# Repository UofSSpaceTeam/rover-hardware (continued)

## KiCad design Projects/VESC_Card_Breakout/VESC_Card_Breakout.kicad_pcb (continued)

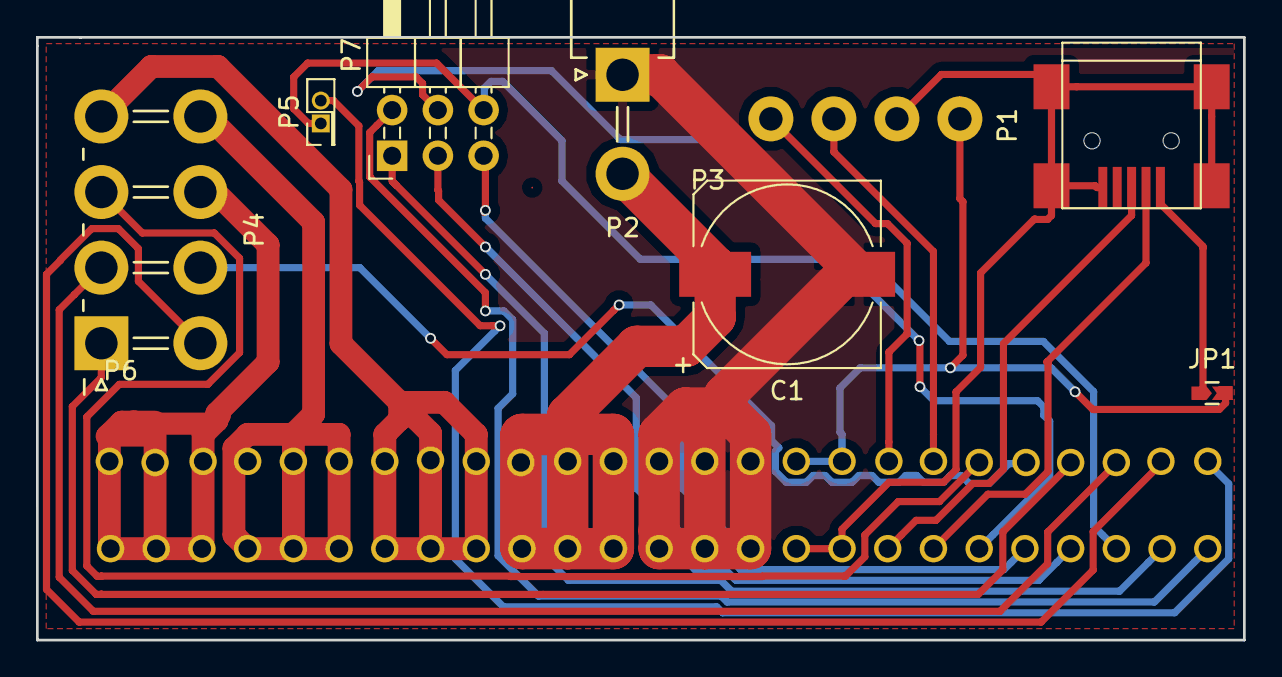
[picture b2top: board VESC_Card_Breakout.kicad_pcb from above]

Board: 2 copper layers, 67.1 x 33.5 mm, 9 parts (0 on the bottom side), 24 nets.

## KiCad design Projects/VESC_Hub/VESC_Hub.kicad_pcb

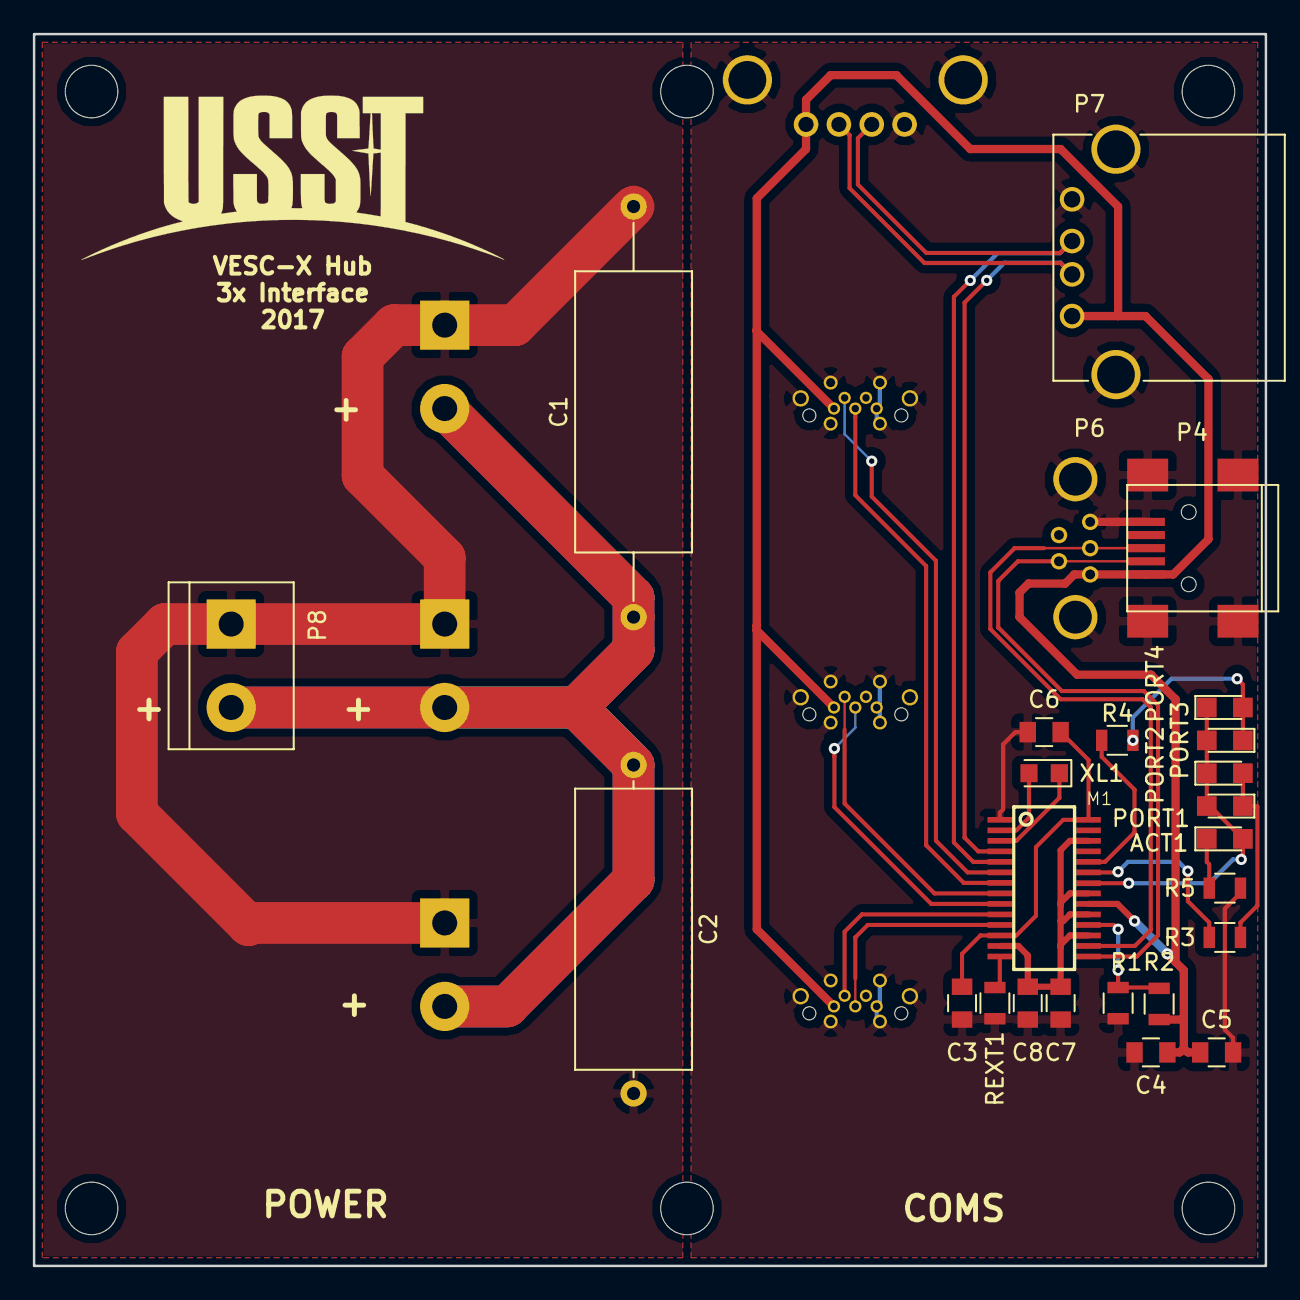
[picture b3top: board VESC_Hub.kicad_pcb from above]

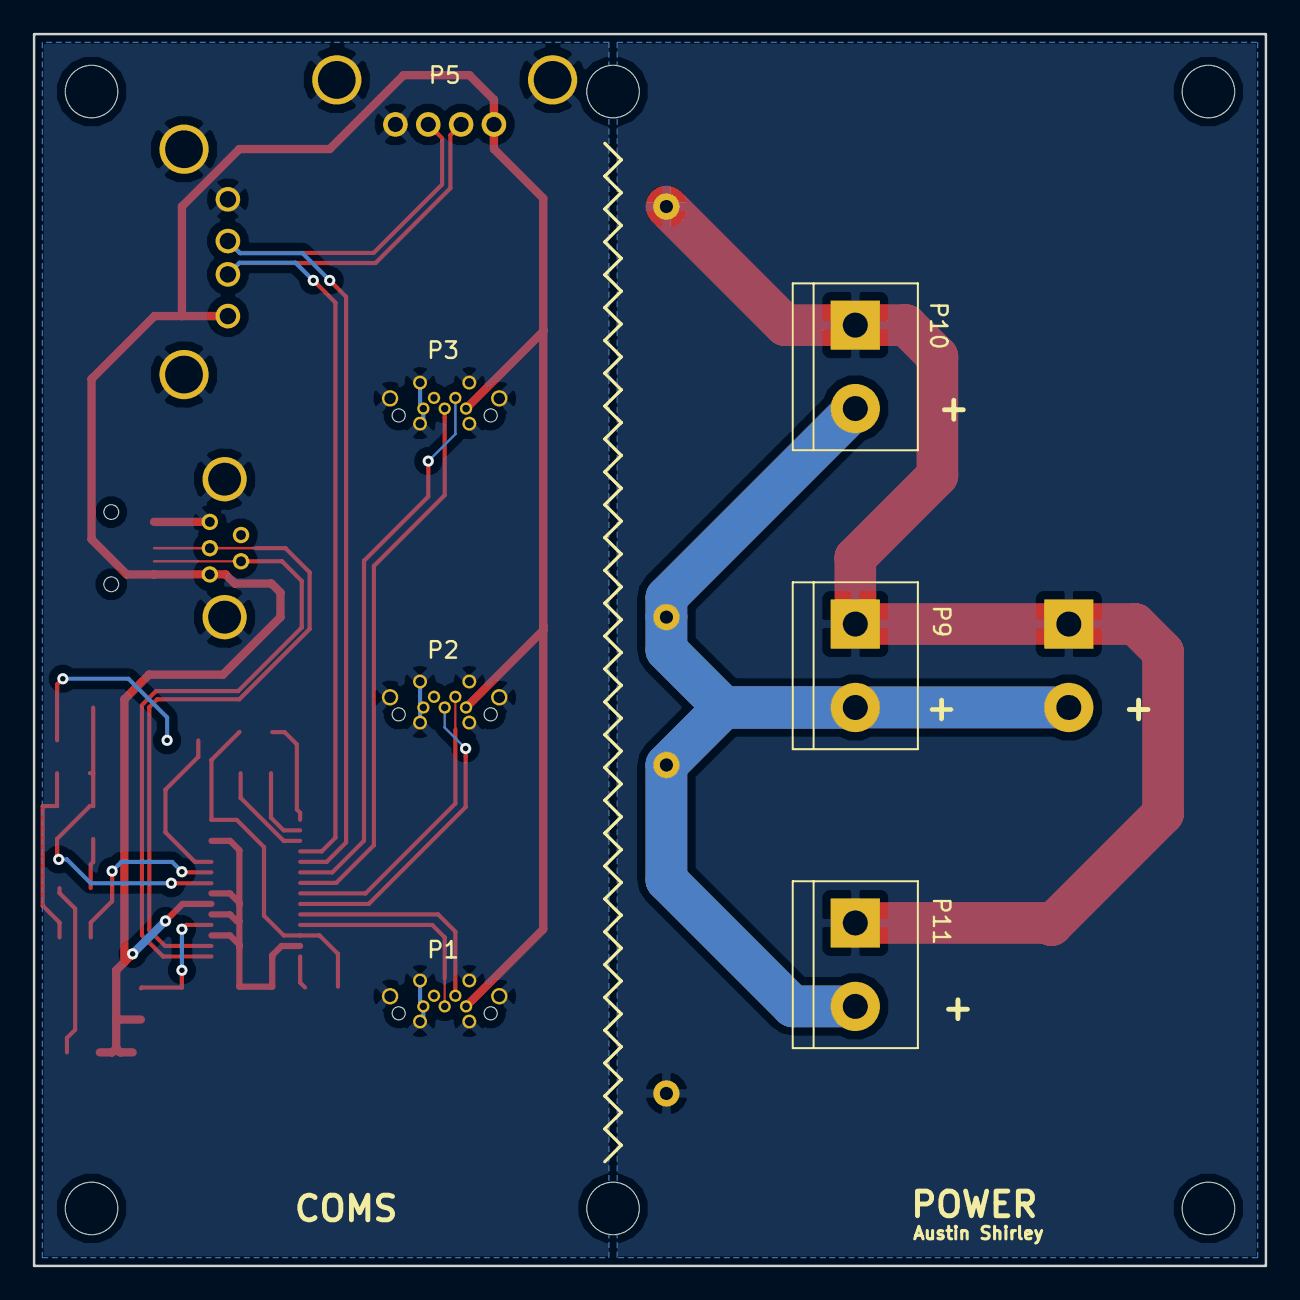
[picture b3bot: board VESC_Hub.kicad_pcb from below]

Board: 2 copper layers, 75.0 x 75.0 mm, 32 parts (7 on the bottom side), 26 nets.

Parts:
ACT1: LED_0805
C1: 2000u; C_Axial_L17.0mm_D7.0mm_P25.00mm_Horizontal
C2: 2000u; C_Axial_L17.0mm_D7.0mm_P20.00mm_Horizontal
C3, C4, C7: 10uF; C_0805
C5, C6, C8: 0.1uF; C_0805
M1: FE1.1S; FE1.1S_SSOP-28
P1: USB_OTG_M1; USB3150_Micro_Vertical
P2: USB_OTG_M2; USB3150_Micro_Vertical
P3: USB_OTG_M3; USB3150_Micro_Vertical
P4: USB_OTG_UP; USB_Mini-B
P5: USB_DS; WRCOM_USB_A_VERT
P6: USB_OTG_UP; WRCOM_MINI_USB_VERT
P7: USB_DS; USB_A
P8: POWER_IN; bornier2
P9: M1; bornier2
P10: M2; bornier2
P11: M3; bornier2
PORT1, PORT2, PORT3, PORT4: LED_0805
R1: 100K; R_0805
R2: 47K; R_0805
R3, R4, R5: 330; R_0805
REXT1: 2.7K; R_0805
XL1: 12MHz; Crystal_SMD_2012-2pin_2.0x1.2mm_HandSoldering

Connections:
+5V: C4.1, C5.1, M1.20, P1.1, P2.1, P3.1, P4.1, P5.1, P6.1, P7.1, R2.1
+24V: C1.1, C2.1, P8.2, P9.2, P10.2, P11.2
/USB1_N: M1.4, P5.2, P7.2
/USB1_P: M1.5, P5.3, P7.3
/USB2_N: M1.6, P3.2
/USB2_P: M1.7, P3.3
/USB3_N: M1.8, P2.2
/USB3_P: M1.9, P2.3
/USB4_N: M1.10, P1.2
/USB4_P: M1.11, P1.3
/USBUP_N: M1.15, P4.2, P6.2
/USBUP_P: M1.16, P4.3, P6.3
GND: C1.2, C2.2, P8.1, P9.1, P10.1, P11.1
GNDD: C3.2, C4.2, C5.2, C6.2, C7.2, C8.2, M1.1, P1.5, P1.6, P2.5, P2.6, P3.5, P3.6, P4.5, P4.6, P5.4, P5.5, P6.5, P6.6, P7.4, P7.5, R1.2, R5.2, REXT1.1
unnamed: ACT1.1, R5.1
unnamed: ACT1.2, M1.22, PORT1.2, PORT2.1, PORT3.2, PORT4.1
unnamed: C3.1, C6.1, M1.12, M1.28
unnamed: M1.2, XL1.2
unnamed: M1.3, XL1.1
unnamed: M1.14, REXT1.2
unnamed: M1.18, R1.1, R2.2
unnamed: M1.23, R3.1
unnamed: M1.24, R4.1
unnamed: PORT1.1, PORT2.2, R3.2
unnamed: PORT3.1, PORT4.2, R4.2
VDD: C7.1, C8.1, M1.13, M1.17, M1.19, M1.21, M1.26

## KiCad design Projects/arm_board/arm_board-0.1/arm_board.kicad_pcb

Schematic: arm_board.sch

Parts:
DEMUX1: 74HC138; SO-16-N
MUX1, MUX2, MUX3: 74HC4051; SO-16-N
P3, P4: CONN_2; MiniFitJr_2-pin_0039310028
U1: TLV150X; SO-16-N
U2: 7805; MC7805CDTRKG
U56: 2534-6002UB_34-pin_header; 34-pin_2534-6002UB

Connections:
12V: P3.1, U2.1; also elsewhere on the board
/EOC_MCU: U1.4 (EOC), U56.26
/MCU_FS: U1.13 (FS), U56.14
/MCU_SCLK: U1.3 (SCLK), U56.8
/MCU_SDI: U1.1 (SDO), U56.12
/MCU_SDO: U1.2 (SDI), U56.10
/OIL_ss/CLR: U56.6; also elsewhere on the board
/OIL_ss/D: U56.4; also elsewhere on the board
/OIL_ss/EN: U56.2; also elsewhere on the board
/OIL_ss/MCU_PWM0: U56.9; also elsewhere on the board
/OIL_ss/MCU_PWM1: U56.11; also elsewhere on the board
/OIL_ss/MCU_PWM2: U56.13; also elsewhere on the board
/OIL_ss/MCU_PWM3: U56.15; also elsewhere on the board
/OIL_ss/MCU_PWM4: U56.17; also elsewhere on the board
/OIL_ss/MCU_PWM5: U56.19; also elsewhere on the board
/OIL_ss/MCU_PWM6: U56.21; also elsewhere on the board
/OIL_ss/MCU_PWM7: U56.23; also elsewhere on the board
/OIL_ss/S0: DEMUX1.1 (A0), MUX1.11 (S0), MUX2.11 (S0), MUX3.11 (S0), U56.16; also elsewhere on the board
/OIL_ss/S1: DEMUX1.2 (A1), MUX1.10 (S1), MUX2.10 (S1), MUX3.10 (S1), U56.18; also elsewhere on the board
/OIL_ss/S2: DEMUX1.3 (A2), MUX1.9 (S2), MUX2.9 (S2), MUX3.9 (S2), U56.20; also elsewhere on the board
/OVRFLW: MUX2.3 (Z), U56.27
/Q_CNT: MUX1.3 (Z), U56.25
/RST: DEMUX1.6 (E3), U56.31
/UDRFLW: MUX3.3 (Z), U56.29
/VNH3SP30 Motor SS 1/CNT_OVRFLW: MUX2.14 (Y1); also elsewhere on the board
/VNH3SP30 Motor SS 1/CNT_S0: U56.1; also elsewhere on the board
/VNH3SP30 Motor SS 1/CNT_S1: U56.3; also elsewhere on the board
/VNH3SP30 Motor SS 1/CNT_S2: U56.5; also elsewhere on the board
/VNH3SP30 Motor SS 1/CNT_S3: U56.7; also elsewhere on the board
/VNH3SP30 Motor SS 1/CNT_UDRFLW: MUX3.14 (Y1); also elsewhere on the board
/VNH3SP30 Motor SS 1/Q_CNT: MUX1.14 (Y1); also elsewhere on the board
/VNH3SP30 Motor SS 1/n_CNT_RESET: DEMUX1.14 (n_Y1); also elsewhere on the board
/VNH3SP30 Motor SS 2/CNT_OVRFLW: MUX2.15 (Y2); also elsewhere on the board
/VNH3SP30 Motor SS 2/CNT_UDRFLW: MUX3.15 (Y2); also elsewhere on the board
/VNH3SP30 Motor SS 2/Q_CNT: MUX1.15 (Y2); also elsewhere on the board
/VNH3SP30 Motor SS 2/n_CNT_RESET: DEMUX1.13 (n_Y2); also elsewhere on the board
/VNH3SP30 Motor SS 3/CNT_OVRFLW: MUX2.12 (Y3); also elsewhere on the board
/VNH3SP30 Motor SS 3/CNT_UDRFLW: MUX3.12 (Y3); also elsewhere on the board
/VNH3SP30 Motor SS 3/Q_CNT: MUX1.12 (Y3); also elsewhere on the board
/VNH3SP30 Motor SS 3/n_CNT_RESET: DEMUX1.12 (n_Y3); also elsewhere on the board
/VNH3SP30 Motor SS 4/CNT_OVRFLW: MUX2.1 (Y4); also elsewhere on the board
/VNH3SP30 Motor SS 4/CNT_UDRFLW: MUX3.1 (Y4); also elsewhere on the board
/VNH3SP30 Motor SS 4/Q_CNT: MUX1.1 (Y4); also elsewhere on the board
/VNH3SP30 Motor SS 4/n_CNT_RESET: DEMUX1.11 (n_Y4); also elsewhere on the board
/VNH3SP30 Motor SS 5/CNT_OVRFLW: MUX2.5 (Y5); also elsewhere on the board
/VNH3SP30 Motor SS 5/CNT_UDRFLW: MUX3.5 (Y5); also elsewhere on the board
/VNH3SP30 Motor SS 5/Q_CNT: MUX1.5 (Y5); also elsewhere on the board
/VNH3SP30 Motor SS 5/n_CNT_RESET: DEMUX1.10 (n_Y5); also elsewhere on the board
/VNH3SP30 SS 1/WPR: U1.6 (A0), U56.33; also elsewhere on the board
/VNH3SP30 SS 2/WPR: U1.7 (A1), U56.32; also elsewhere on the board
/n_ADC_CS: U1.16 (n_CS), U56.24
/n_ADC_CSTART: U1.10 (n_CSTART), U56.22
/vnh3sp30_motorLinac_ss/CNT_OVRFLW: MUX2.13 (Y0); also elsewhere on the board
/vnh3sp30_motorLinac_ss/CNT_UDRFLW: MUX3.13 (Y0); also elsewhere on the board
/vnh3sp30_motorLinac_ss/Q_CNT: MUX1.13 (Y0); also elsewhere on the board
/vnh3sp30_motorLinac_ss/WPR: U1.8 (A2), U56.34; also elsewhere on the board
/vnh3sp30_motorLinac_ss/n_CNT_RESET: DEMUX1.15 (n_Y0); also elsewhere on the board
GND_12V: P3.2 (PM), U2.2; also elsewhere on the board
NOISE_5V: U2.3; also elsewhere on the board
unnamed 225: DEMUX1.7 (n_Y7); also elsewhere on the board
unnamed 226: DEMUX1.9 (n_Y6); also elsewhere on the board
Whiper_GND: U1.14 (REFM), U56.28; also elsewhere on the board
Whiper_V++: U1.15 (REFP), U56.30; also elsewhere on the board

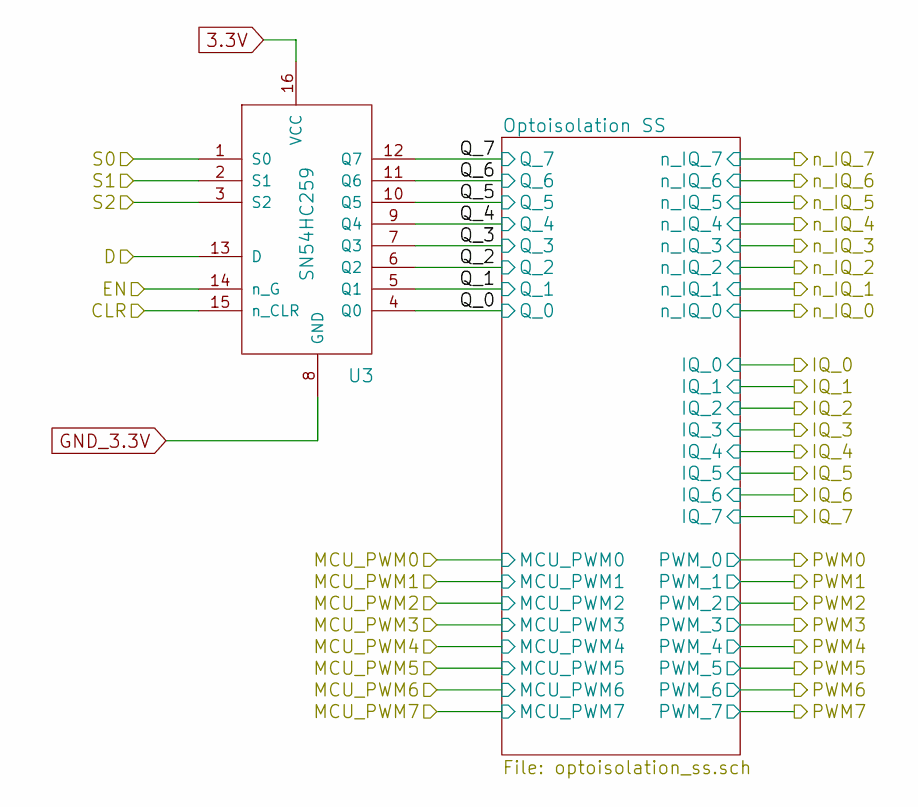
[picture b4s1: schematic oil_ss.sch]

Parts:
U3: SN54HC259; SO-16-N

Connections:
/OIL_ss/CLR: U3.15 (n_CLR); also elsewhere on the board
/OIL_ss/D: U3.13 (D); also elsewhere on the board
/OIL_ss/EN: U3.14 (n_G); also elsewhere on the board
/OIL_ss/Optoisolation SS/Q_0: U3.4 (Q0); also elsewhere on the board
/OIL_ss/Optoisolation SS/Q_1: U3.5 (Q1); also elsewhere on the board
/OIL_ss/Optoisolation SS/Q_2: U3.6 (Q2); also elsewhere on the board
/OIL_ss/Optoisolation SS/Q_3: U3.7 (Q3); also elsewhere on the board
/OIL_ss/Optoisolation SS/Q_4: U3.9 (Q4); also elsewhere on the board
/OIL_ss/Optoisolation SS/Q_5: U3.10 (Q5); also elsewhere on the board
/OIL_ss/Optoisolation SS/Q_6: U3.11 (Q6); also elsewhere on the board
/OIL_ss/Optoisolation SS/Q_7: U3.12 (Q7); also elsewhere on the board
/OIL_ss/S0: U3.1 (S0); also elsewhere on the board
/OIL_ss/S1: U3.2 (S1); also elsewhere on the board
/OIL_ss/S2: U3.3 (S2); also elsewhere on the board

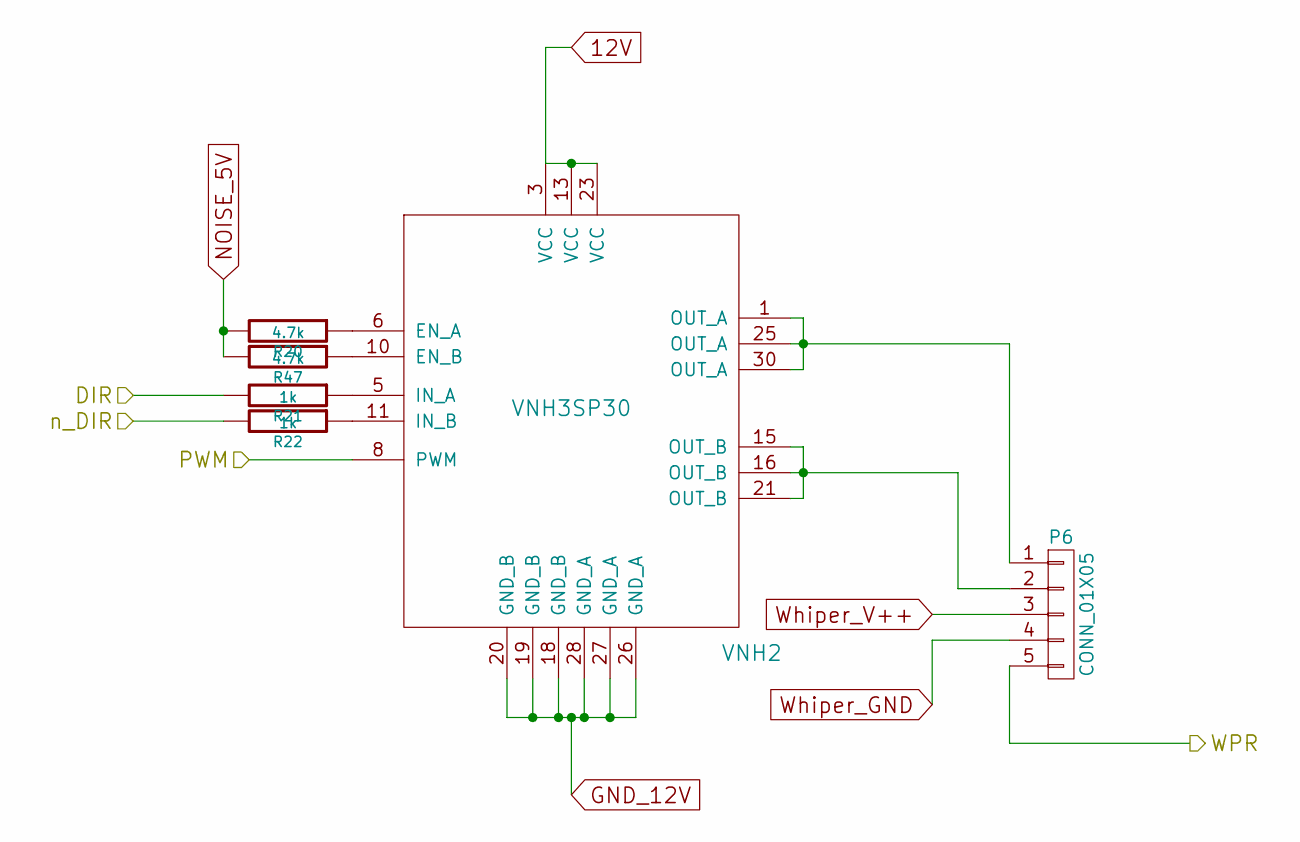
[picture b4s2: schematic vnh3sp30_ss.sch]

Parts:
P5: CONN_01X05; 5-pin_640467-1
R17, R46: 4.7k; R_0805
R18, R22: 1k; R_0805
VNH1: VNH3SP30; VNH3SP30TR-E

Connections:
12V: VNH1.3 (VCC), VNH1.13 (VCC), VNH1.23 (VCC); also elsewhere on the board
/VNH3SP30 SS 1/DIR: R18.2; also elsewhere on the board
/VNH3SP30 SS 1/PWM: VNH1.8 (PWM); also elsewhere on the board
/VNH3SP30 SS 1/WPR: P5.5; also elsewhere on the board
/VNH3SP30 SS 2/n_DIR: R22.2; also elsewhere on the board
GND_12V: VNH1.18 (GND_B), VNH1.19 (GND_B), VNH1.20 (GND_B), VNH1.26 (GND_A), VNH1.27 (GND_A), VNH1.28 (GND_A); also elsewhere on the board
NOISE_5V: R17.2, R46.2; also elsewhere on the board
unnamed: P5.1, VNH1.1 (OUT_A), VNH1.25 (OUT_A), VNH1.30 (OUT_A)
unnamed: P5.2, VNH1.15 (OUT_B), VNH1.16 (OUT_B), VNH1.21 (OUT_B)
unnamed: R17.1, VNH1.6 (EN_A)
unnamed: R18.1, VNH1.5 (IN_A)
unnamed: R46.1, VNH1.10 (EN_B)
Whiper_GND: P5.4; also elsewhere on the board
Whiper_V++: P5.3; also elsewhere on the board

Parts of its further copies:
P6: CONN_01X05; 5-pin_640467-1
R19, R21: 1k; R_0805
R20, R47: 4.7k; R_0805
VNH2: VNH3SP30; VNH3SP30TR-E

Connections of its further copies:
12V: VNH2.3 (VCC), VNH2.13 (VCC), VNH2.23 (VCC); also elsewhere on the board
/VNH3SP30 SS 1/n_DIR: R19.2; also elsewhere on the board
/VNH3SP30 SS 2/DIR: R21.2; also elsewhere on the board
/VNH3SP30 SS 2/PWM: VNH2.8 (PWM); also elsewhere on the board
/VNH3SP30 SS 2/WPR: P6.5; also elsewhere on the board
GND_12V: VNH2.18 (GND_B), VNH2.19 (GND_B), VNH2.20 (GND_B), VNH2.26 (GND_A), VNH2.27 (GND_A), VNH2.28 (GND_A); also elsewhere on the board
NOISE_5V: R20.2, R47.2; also elsewhere on the board
unnamed: P6.1, VNH2.1 (OUT_A), VNH2.25 (OUT_A), VNH2.30 (OUT_A)
unnamed: P6.2, VNH2.15 (OUT_B), VNH2.16 (OUT_B), VNH2.21 (OUT_B)
unnamed: R20.1, VNH2.6 (EN_A)
unnamed: R21.1, VNH2.5 (IN_A)
unnamed: R47.1, VNH2.10 (EN_B)
Whiper_GND: P6.4; also elsewhere on the board
Whiper_V++: P6.3; also elsewhere on the board

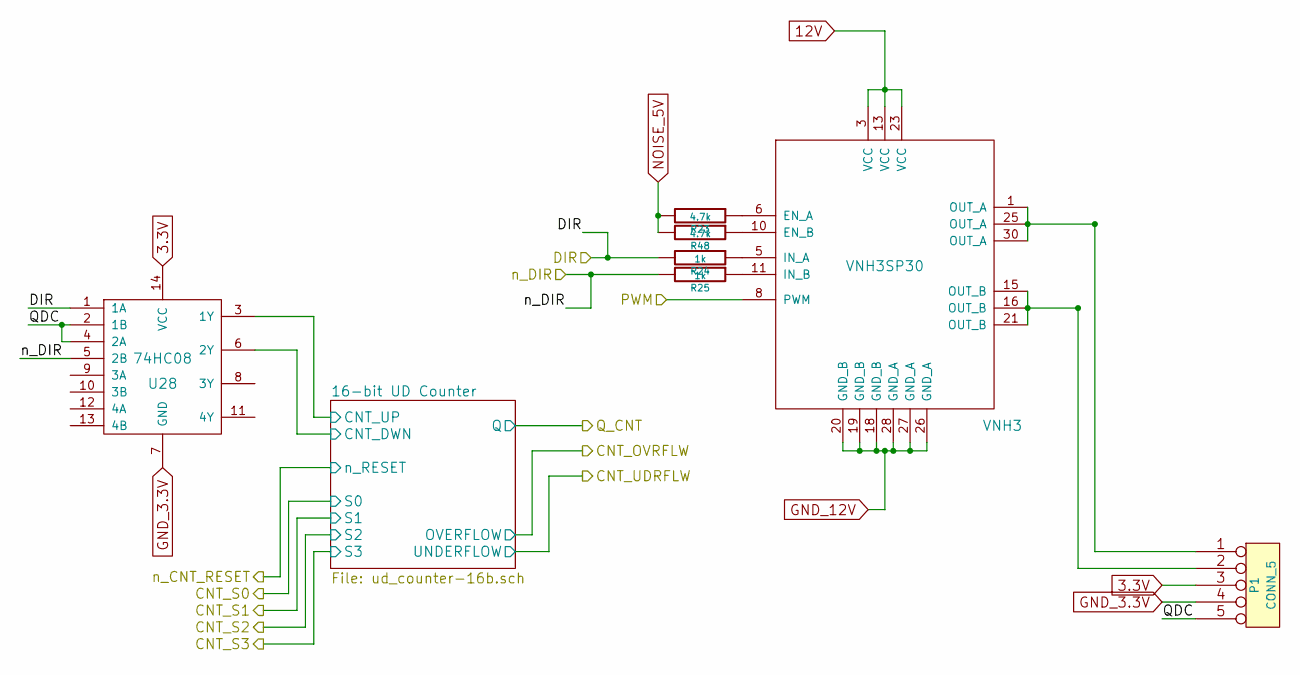
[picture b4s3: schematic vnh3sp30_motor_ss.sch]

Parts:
P1: CONN_5; 5-pin_640467-1
R23, R53: 4.7k; R_0805
R39, R40: 1k; R_0805
U28: 74HC08; SOIC-14
VNH3: VNH3SP30; VNH3SP30TR-E

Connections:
12V: VNH3.3 (VCC), VNH3.13 (VCC), VNH3.23 (VCC); also elsewhere on the board
/VNH3SP30 Motor SS 1/16-bit UD Counter/CNT_DWN: U28.6 (2Y); also elsewhere on the board
/VNH3SP30 Motor SS 1/16-bit UD Counter/CNT_UP: U28.3 (1Y); also elsewhere on the board
/VNH3SP30 Motor SS 1/PWM: VNH3.8 (PWM); also elsewhere on the board
/VNH3SP30 Motor SS 1/QDC: P1.5, U28.2 (1B), U28.4 (2A)
GND_12V: VNH3.18 (GND_B), VNH3.19 (GND_B), VNH3.20 (GND_B), VNH3.26 (GND_A), VNH3.27 (GND_A), VNH3.28 (GND_A); also elsewhere on the board
NOISE_5V: R23.2, R53.2; also elsewhere on the board
unnamed: P1.1, VNH3.1 (OUT_A), VNH3.25 (OUT_A), VNH3.30 (OUT_A)
unnamed: P1.2, VNH3.15 (OUT_B), VNH3.16 (OUT_B), VNH3.21 (OUT_B)
unnamed: R23.1, VNH3.6 (EN_A)

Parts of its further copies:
P2, P7, P8, P10: CONN_5; 5-pin_640467-1
R24, R25, R27, R28, R30, R31, R33, R34: 1k; R_0805
R26, R29, R32, R38, R48, R49, R50, R51: 4.7k; R_0805
U35, U42, U44, U58: 74HC08; SOIC-14
VNH4, VNH5, VNH6, VNH7: VNH3SP30; VNH3SP30TR-E

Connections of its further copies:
12V: VNH4.3 (VCC), VNH4.13 (VCC), VNH4.23 (VCC), VNH5.3 (VCC), VNH5.13 (VCC), VNH5.23 (VCC), VNH6.3 (VCC), VNH6.13 (VCC), VNH6.23 (VCC), VNH7.3 (VCC), VNH7.13 (VCC), VNH7.23 (VCC); also elsewhere on the board
/VNH3SP30 Motor SS 2/16-bit UD Counter/CNT_DWN: U58.6 (2Y); also elsewhere on the board
/VNH3SP30 Motor SS 2/16-bit UD Counter/CNT_UP: U58.3 (1Y); also elsewhere on the board
/VNH3SP30 Motor SS 2/PWM: VNH4.8 (PWM); also elsewhere on the board
/VNH3SP30 Motor SS 2/QDC: P10.5, U58.2 (1B), U58.4 (2A)
/VNH3SP30 Motor SS 3/16-bit UD Counter/CNT_DWN: U35.6 (2Y); also elsewhere on the board
/VNH3SP30 Motor SS 3/16-bit UD Counter/CNT_UP: U35.3 (1Y); also elsewhere on the board
/VNH3SP30 Motor SS 3/DIR: R27.2, U35.1 (1A); also elsewhere on the board
/VNH3SP30 Motor SS 3/PWM: VNH5.8 (PWM); also elsewhere on the board
/VNH3SP30 Motor SS 3/QDC: P2.5, U35.2 (1B), U35.4 (2A)
/VNH3SP30 Motor SS 3/n_DIR: R28.2, U35.5 (2B); also elsewhere on the board
/VNH3SP30 Motor SS 4/16-bit UD Counter/CNT_DWN: U44.6 (2Y); also elsewhere on the board
/VNH3SP30 Motor SS 4/16-bit UD Counter/CNT_UP: U44.3 (1Y); also elsewhere on the board
/VNH3SP30 Motor SS 4/DIR: R33.2, U44.1 (1A); also elsewhere on the board
/VNH3SP30 Motor SS 4/PWM: VNH7.8 (PWM); also elsewhere on the board
/VNH3SP30 Motor SS 4/QDC: P8.5, U44.2 (1B), U44.4 (2A)
/VNH3SP30 Motor SS 4/n_DIR: R34.2, U44.5 (2B); also elsewhere on the board
/VNH3SP30 Motor SS 5/16-bit UD Counter/CNT_DWN: U42.6 (2Y); also elsewhere on the board
/VNH3SP30 Motor SS 5/16-bit UD Counter/CNT_UP: U42.3 (1Y); also elsewhere on the board
/VNH3SP30 Motor SS 5/DIR: R30.2, U42.1 (1A); also elsewhere on the board
/VNH3SP30 Motor SS 5/PWM: VNH6.8 (PWM); also elsewhere on the board
/VNH3SP30 Motor SS 5/QDC: P7.5, U42.2 (1B), U42.4 (2A)
/VNH3SP30 Motor SS 5/n_DIR: R31.2, U42.5 (2B); also elsewhere on the board
GND_12V: VNH4.18 (GND_B), VNH4.19 (GND_B), VNH4.20 (GND_B), VNH4.26 (GND_A), VNH4.27 (GND_A), VNH4.28 (GND_A), VNH5.18 (GND_B), VNH5.19 (GND_B), VNH5.20 (GND_B), VNH5.26 (GND_A), VNH5.27 (GND_A), VNH5.28 (GND_A), VNH6.18 (GND_B), VNH6.19 (GND_B), VNH6.20 (GND_B), VNH6.26 (GND_A), VNH6.27 (GND_A), VNH6.28 (GND_A), VNH7.18 (GND_B), VNH7.19 (GND_B), VNH7.20 (GND_B), VNH7.26 (GND_A), VNH7.27 (GND_A), VNH7.28 (GND_A); also elsewhere on the board
NOISE_5V: R26.2, R29.2, R32.2, R38.2, R48.2, R49.2, R50.2, R51.2; also elsewhere on the board
unnamed: P2.1, VNH5.1 (OUT_A), VNH5.25 (OUT_A), VNH5.30 (OUT_A)
unnamed: P2.2, VNH5.15 (OUT_B), VNH5.16 (OUT_B), VNH5.21 (OUT_B)
unnamed: P7.1, VNH6.1 (OUT_A), VNH6.25 (OUT_A), VNH6.30 (OUT_A)
unnamed: P7.2, VNH6.15 (OUT_B), VNH6.16 (OUT_B), VNH6.21 (OUT_B)
unnamed: P8.1, VNH7.1 (OUT_A), VNH7.25 (OUT_A), VNH7.30 (OUT_A)
unnamed: P8.2, VNH7.15 (OUT_B), VNH7.16 (OUT_B), VNH7.21 (OUT_B)
unnamed: P10.1, VNH4.1 (OUT_A), VNH4.25 (OUT_A), VNH4.30 (OUT_A)
unnamed: P10.2, VNH4.15 (OUT_B), VNH4.16 (OUT_B), VNH4.21 (OUT_B)
unnamed: R26.1, VNH5.6 (EN_A)
unnamed: R27.1, VNH5.5 (IN_A)
unnamed: R28.1, VNH5.11 (IN_B)
unnamed: R29.1, VNH6.6 (EN_A)
unnamed: R30.1, VNH6.5 (IN_A)
unnamed: R31.1, VNH6.11 (IN_B)
unnamed: R32.1, VNH7.6 (EN_A)
unnamed: R33.1, VNH7.5 (IN_A)
unnamed: R34.1, VNH7.11 (IN_B)
unnamed: R38.1, VNH4.6 (EN_A)
unnamed: R49.1, VNH5.10 (EN_B)
unnamed: R50.1, VNH6.10 (EN_B)
unnamed: R51.1, VNH7.10 (EN_B)

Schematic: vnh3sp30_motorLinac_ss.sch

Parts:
P9: CONN_4X2; MiniFitJr_8-pin_0050348563
R35: 4.7k; R_0805
R36, R37: 1k; R_0805
U57: 74HC08; SOIC-14_N
VNH8: VNH3SP30; VNH3SP30TR-E

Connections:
12V: VNH8.3 (VCC), VNH8.13 (VCC), VNH8.23 (VCC); also elsewhere on the board
/vnh3sp30_motorLinac_ss/16-bit UD Counter/CNT_DWN: U57.6 (2Y); also elsewhere on the board
/vnh3sp30_motorLinac_ss/16-bit UD Counter/CNT_UP: U57.3 (1Y); also elsewhere on the board
/vnh3sp30_motorLinac_ss/DIR: R36.2, U57.1 (1A); also elsewhere on the board
/vnh3sp30_motorLinac_ss/PWM: VNH8.8 (PWM); also elsewhere on the board
/vnh3sp30_motorLinac_ss/QDC: P9.5, U57.2 (1B), U57.4 (2A)
/vnh3sp30_motorLinac_ss/n_DIR: R37.2, U57.5 (2B); also elsewhere on the board
GND_12V: VNH8.18 (GND_B), VNH8.19 (GND_B), VNH8.20 (GND_B), VNH8.26 (GND_A), VNH8.27 (GND_A), VNH8.28 (GND_A); also elsewhere on the board
NOISE_5V: R35.2; also elsewhere on the board
unnamed 241: P9.1, VNH8.1 (OUT_A), VNH8.25 (OUT_A), VNH8.30 (OUT_A); also elsewhere on the board
unnamed 242: P9.2, VNH8.15 (OUT_B), VNH8.16 (OUT_B), VNH8.21 (OUT_B); also elsewhere on the board
unnamed: R36.1, VNH8.5 (IN_A)
unnamed: R37.1, VNH8.11 (IN_B)

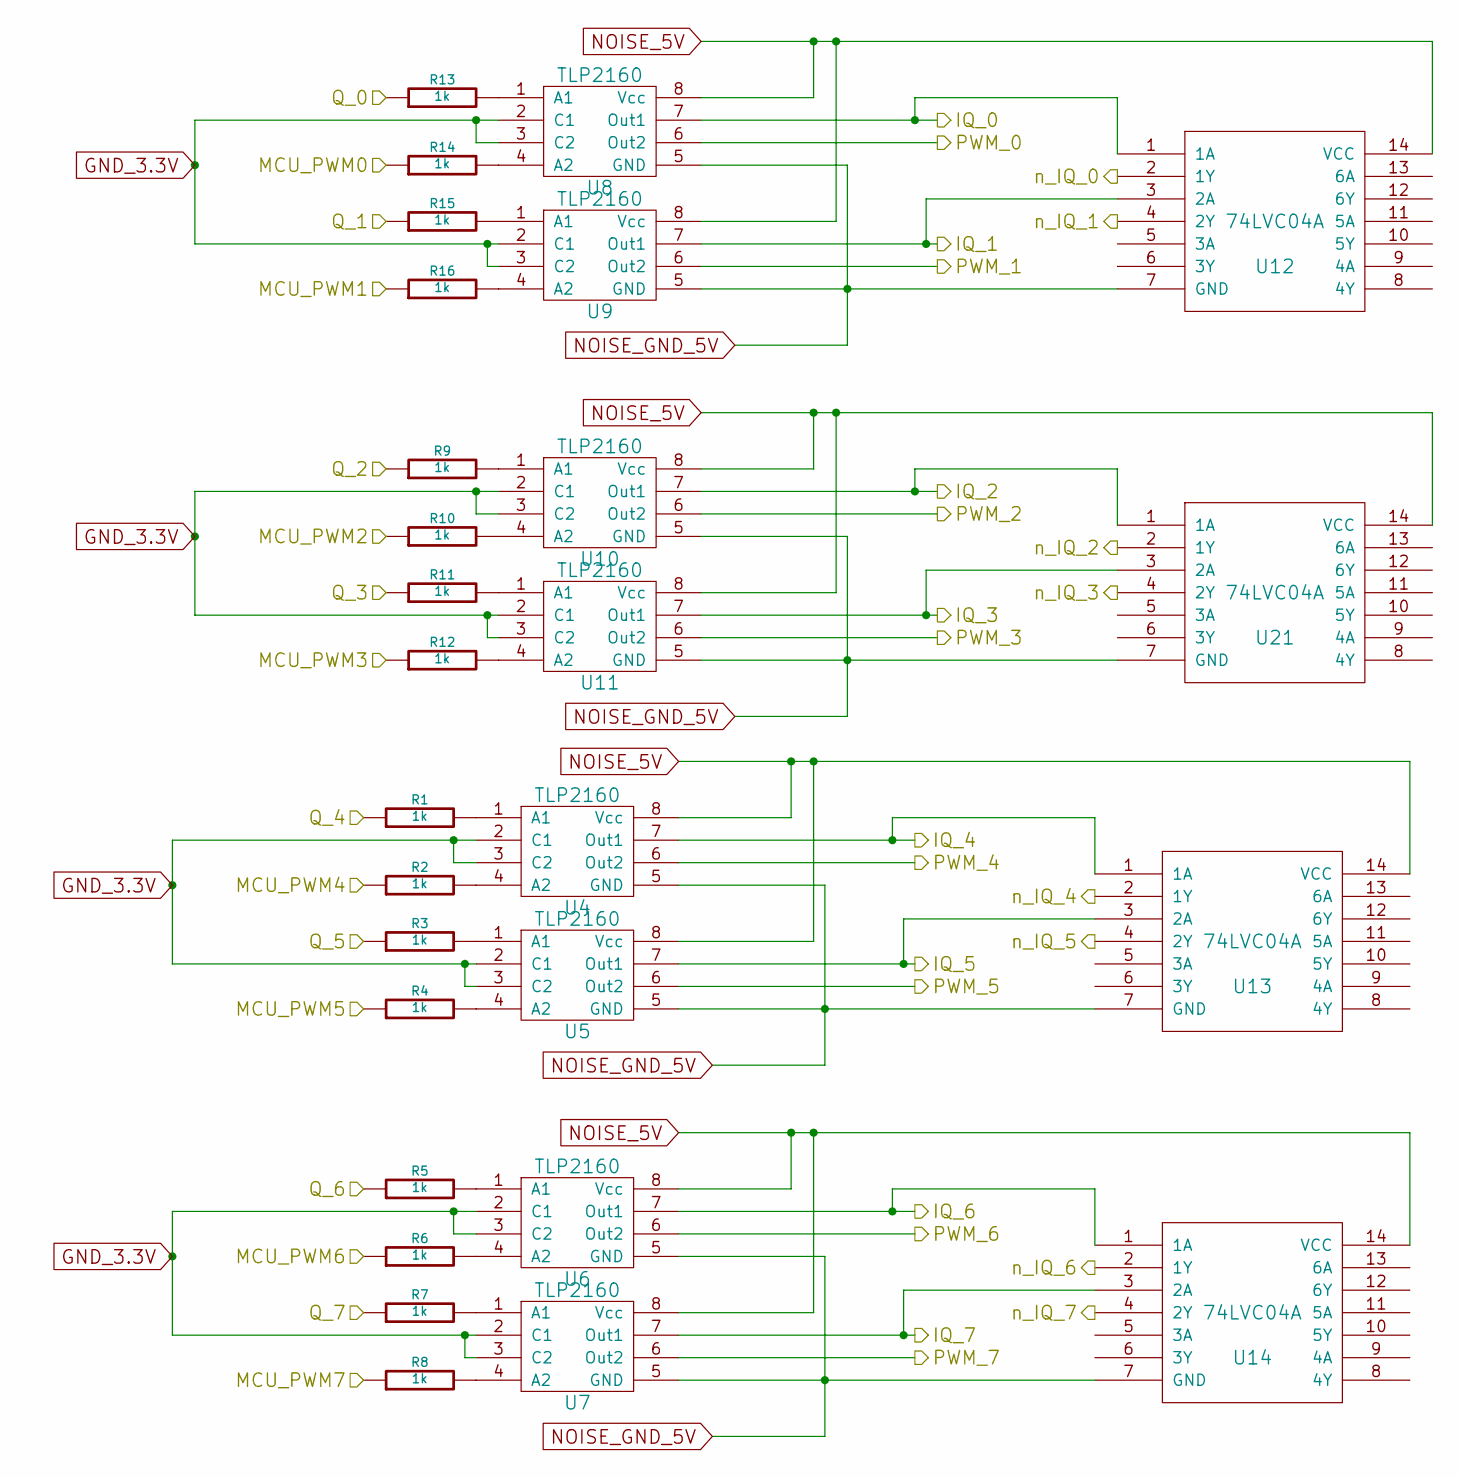
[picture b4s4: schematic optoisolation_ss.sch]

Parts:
R1, R2, R3, R4, R5, R6, R7, R8, R9, R10, R11, R12, R13, R14, R15, R16: 1k; R_0805
U4, U5, U6, U7, U8, U9, U10, U11: TLP2160
U12, U13, U14, U21: 74LVC04A; SOIC-14

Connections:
/OIL_ss/MCU_PWM0: R14.1; also elsewhere on the board
/OIL_ss/MCU_PWM1: R16.1; also elsewhere on the board
/OIL_ss/MCU_PWM2: R10.1; also elsewhere on the board
/OIL_ss/MCU_PWM3: R12.1; also elsewhere on the board
/OIL_ss/MCU_PWM4: R2.1; also elsewhere on the board
/OIL_ss/MCU_PWM5: R4.1; also elsewhere on the board
/OIL_ss/MCU_PWM6: R6.1; also elsewhere on the board
/OIL_ss/MCU_PWM7: R8.1; also elsewhere on the board
/OIL_ss/Optoisolation SS/Q_0: R13.1; also elsewhere on the board
/OIL_ss/Optoisolation SS/Q_1: R15.1; also elsewhere on the board
/OIL_ss/Optoisolation SS/Q_2: R9.1; also elsewhere on the board
/OIL_ss/Optoisolation SS/Q_3: R11.1; also elsewhere on the board
/OIL_ss/Optoisolation SS/Q_4: R1.1; also elsewhere on the board
/OIL_ss/Optoisolation SS/Q_5: R3.1; also elsewhere on the board
/OIL_ss/Optoisolation SS/Q_6: R5.1; also elsewhere on the board
/OIL_ss/Optoisolation SS/Q_7: R7.1; also elsewhere on the board
/VNH3SP30 Motor SS 1/PWM: U11.6 (Out2); also elsewhere on the board
/VNH3SP30 Motor SS 2/PWM: U4.6 (Out2); also elsewhere on the board
/VNH3SP30 Motor SS 3/DIR: U5.7 (Out1), U13.3 (2A); also elsewhere on the board
/VNH3SP30 Motor SS 3/PWM: U5.6 (Out2); also elsewhere on the board
/VNH3SP30 Motor SS 3/n_DIR: U13.4 (2Y); also elsewhere on the board
/VNH3SP30 Motor SS 4/DIR: U6.7 (Out1), U14.1 (1A); also elsewhere on the board
/VNH3SP30 Motor SS 4/PWM: U6.6 (Out2); also elsewhere on the board
/VNH3SP30 Motor SS 4/n_DIR: U14.2 (1Y); also elsewhere on the board
/VNH3SP30 Motor SS 5/DIR: U7.7 (Out1), U14.3 (2A); also elsewhere on the board
/VNH3SP30 Motor SS 5/PWM: U7.6 (Out2); also elsewhere on the board
/VNH3SP30 Motor SS 5/n_DIR: U14.4 (2Y); also elsewhere on the board
/VNH3SP30 SS 1/DIR: U8.7 (Out1), U12.1 (1A); also elsewhere on the board
/VNH3SP30 SS 1/PWM: U8.6 (Out2); also elsewhere on the board
/VNH3SP30 SS 1/n_DIR: U12.2 (1Y); also elsewhere on the board
/VNH3SP30 SS 2/DIR: U9.7 (Out1), U12.3 (2A); also elsewhere on the board
/VNH3SP30 SS 2/PWM: U9.6 (Out2); also elsewhere on the board
/VNH3SP30 SS 2/n_DIR: U12.4 (2Y); also elsewhere on the board
/vnh3sp30_motorLinac_ss/DIR: U10.7 (Out1), U21.1 (1A); also elsewhere on the board
/vnh3sp30_motorLinac_ss/PWM: U10.6 (Out2); also elsewhere on the board
/vnh3sp30_motorLinac_ss/n_DIR: U21.2 (1Y); also elsewhere on the board
GND_12V: U4.5 (GND), U5.5 (GND), U6.5 (GND), U7.5 (GND), U8.5 (GND), U9.5 (GND), U10.5 (GND), U11.5 (GND), U12.7 (GND), U13.7 (GND), U14.7 (GND), U21.7 (GND); also elsewhere on the board
NOISE_5V: U4.8 (Vcc), U5.8 (Vcc), U6.8 (Vcc), U7.8 (Vcc), U8.8 (Vcc), U9.8 (Vcc), U10.8 (Vcc), U11.8 (Vcc), U12.14 (VCC), U13.14 (VCC), U14.14 (VCC), U21.14 (VCC); also elsewhere on the board
unnamed 243: R1.2, U4.1 (A1); also elsewhere on the board
unnamed 244: R2.2, U4.4 (A2); also elsewhere on the board
unnamed 245: R3.2, U5.1 (A1); also elsewhere on the board
unnamed 246: R4.2, U5.4 (A2); also elsewhere on the board
unnamed 247: R5.2, U6.1 (A1); also elsewhere on the board
unnamed 248: R6.2, U6.4 (A2); also elsewhere on the board
unnamed 249: R7.2, U7.1 (A1); also elsewhere on the board
unnamed 250: R8.2, U7.4 (A2); also elsewhere on the board
unnamed 251: R9.2, U10.1 (A1); also elsewhere on the board
unnamed 252: R10.2, U10.4 (A2); also elsewhere on the board
unnamed 253: R11.2, U11.1 (A1); also elsewhere on the board
unnamed 254: R12.2, U11.4 (A2); also elsewhere on the board
unnamed 255: R13.2, U8.1 (A1); also elsewhere on the board
unnamed 256: R14.2, U8.4 (A2); also elsewhere on the board
unnamed 257: R15.2, U9.1 (A1); also elsewhere on the board
unnamed 258: R16.2, U9.4 (A2); also elsewhere on the board
